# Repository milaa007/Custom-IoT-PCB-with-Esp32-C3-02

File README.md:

Project Summary: Custom 4 LayerIoT PCB with ESP32-C3-02 and TP4056 Li-ion Charger
This project involves the design and development of a custom PCB for an IoT application powered by the ESP32-C3-02 SoC. The board includes integrated power management features using the TP4056 Li-ion battery charger IC, enabling efficient and safe charging of a single-cell Li-ion battery.

Key Features
Microcontroller: ESP32-C3-02 SoC for Wi-Fi and BLE connectivity.
Power Management: TP4056 IC for single-cell Li-ion battery charging with thermal regulation.
Battery Protection: Integrated under-voltage lockout and trickle charging.
Sensors and Modules:
BME280 for temperature, humidity, and pressure sensing.
Ambient light and sound sensors.
Mini SD card reader for data storage.
Flash memory for additional storage.
Display: I2C OLED for real-time data visualization.
Power Inputs:
USB-C connector for charging and data transfer.
LiPo battery connector with onboard charging circuitry.
Indicators: LED indicators for charge status (charging and full).

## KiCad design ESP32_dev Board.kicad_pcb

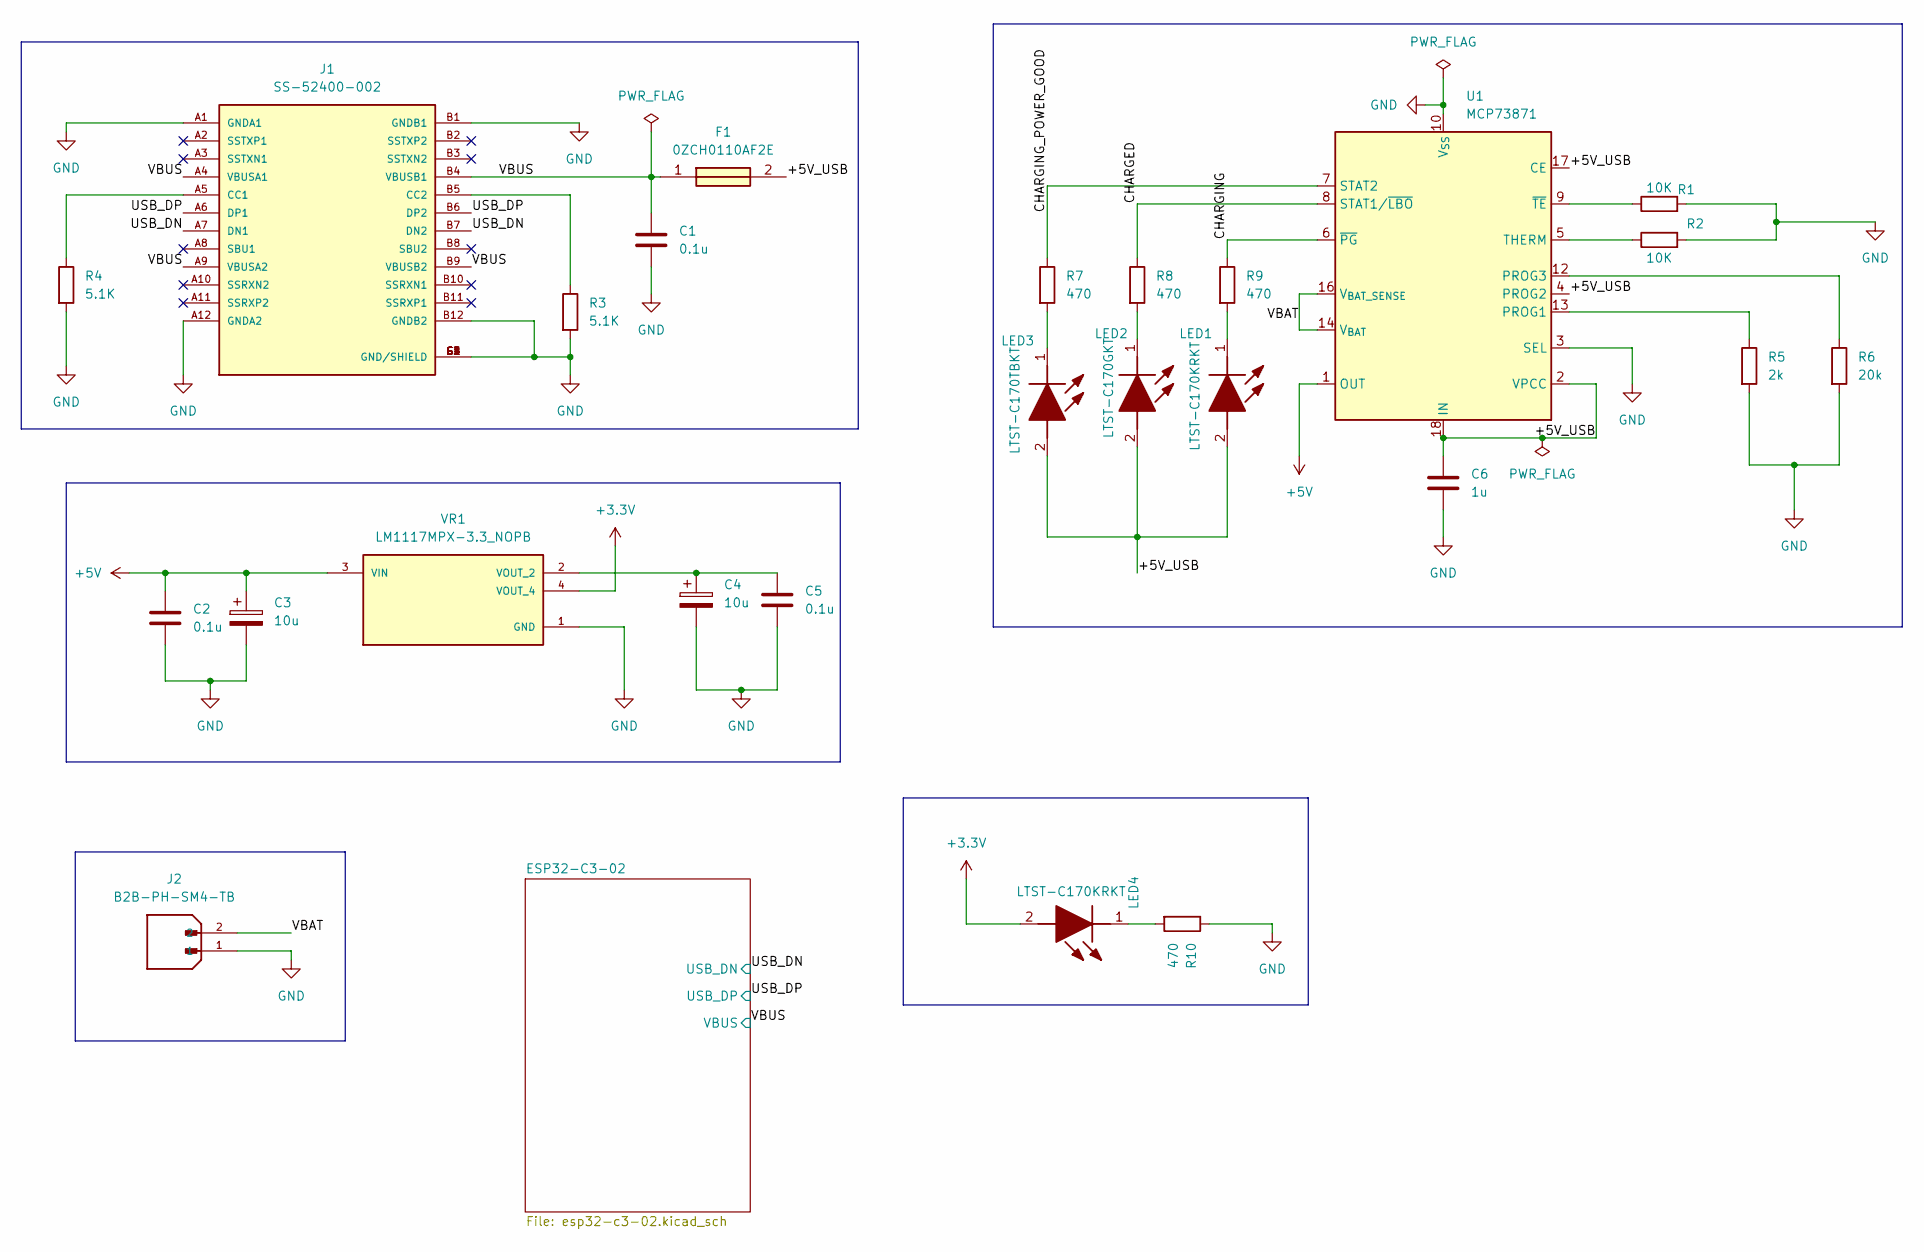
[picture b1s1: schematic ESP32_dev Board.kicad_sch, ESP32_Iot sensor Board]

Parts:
C1, C2, C5: 0.1u; C_0805_2012Metric
C3, C4: 10u; T491A
C6: 1u; C_0805_2012Metric
F1: 0ZCH0110AF2E; FUSC3226X100N; Manufacturer_Part_Number 0ZCH0110AF2E
J1: SS-52400-002; BELFUSE_SS-52400-002; PARTREV A0
J2: B2B-PH-SM4-TB; JST_B2B-PH-SM4-TB; PARTREV N/A
LED1, LED4: LTST-C170KRKT; LEDC2012X120N; Manufacturer_Part_Number LTST-C170KRKT; Mouser Part Number 859-LTST-C170KRKT
LED2: LTST-C170GKT; LEDC2012X120N; Manufacturer_Part_Number LTST-C170GKT; Mouser Part Number 859-LTST-C170GKT
LED3: LTST-C170TBKT; LEDC2012X120N; Manufacturer_Part_Number LTST-C170TBKT; Mouser Part Number 859-LTST-C170TBKT
R1, R2: 10K; R_0805_2012Metric
R3, R4: 5.1K; R_0805_2012Metric
R5: 2k; R_0805_2012Metric
R6: 20k; R_0805_2012Metric
R7, R8, R9, R10: 470; R_0805_2012Metric
U1: MCP73871; QFN-20-1EP_4x4mm_P0.5mm_EP2.5x2.5mm
VR1: LM1117MPX-3.3_NOPB; VREG_LM1117MPX-3.3_NOPB; PARTREV O

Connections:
+5V: C2.1, C3.1, U1.1 (OUT), U1.20 (OUT), VR1.3 (VIN)
/+5V_USB: C6.1, F1.2, LED1.2 (A), LED2.2 (A), LED3.2 (A), U1.2 (VPCC), U1.4 (PROG2), U1.17 (CE), U1.18 (IN), U1.19 (IN)
/CHARGED: R8.1, U1.8 (STAT1/~LBO)
/CHARGING: R9.1, U1.6 (~PG)
/CHARGING_POWER_GOOD: R7.1, U1.7 (STAT2)
/USB_DN: J1.A7 (DN1), J1.B7 (DN2); also elsewhere on the board
/USB_DP: J1.A6 (DP1), J1.B6 (DP2); also elsewhere on the board
/VBAT: J2.2, U1.14 (V_{BAT}), U1.15 (V_{BAT}), U1.16 (V_{BAT_SENSE})
/VBUS: C1.1, F1.1, J1.A4 (VBUSA1), J1.A9 (VBUSA2), J1.B4 (VBUSB1), J1.B9 (VBUSB2); also elsewhere on the board
GND: C1.2, C2.2, C3.2, C4.2, C5.2, C6.2, J1.A1 (GNDA1), J1.A12 (GNDA2), J1.B1 (GNDB1), J1.B12 (GNDB2), J1.G1 (GND/SHIELD), J1.G2 (GND/SHIELD), J1.G3 (GND/SHIELD), J1.G4 (GND/SHIELD), J1.S1 (GND/SHIELD), J1.S2 (GND/SHIELD), J1.S3 (GND/SHIELD), J1.S4 (GND/SHIELD), J2.1, R1.2, R2.2, R3.2, R4.2, R5.2, R6.2, R10.1, U1.3 (SEL), U1.10 (V_{SS}), U1.11 (V_{SS}), U1.21 (V_{SS}), VR1.1 (GND); also elsewhere on the board
unnamed: J1.A5 (CC1), R4.1
unnamed: J1.B5 (CC2), R3.1
unnamed: LED1.1 (K), R9.2
unnamed: LED2.1 (K), R8.2
unnamed: LED3.1 (K), R7.2
unnamed: LED4.1 (K), R10.2
unnamed: R5.1, U1.13 (PROG1)
unnamed: R6.1, U1.12 (PROG3)
unnamed: R2.1, U1.5 (THERM)
unnamed: R1.1, U1.9 (~TE)

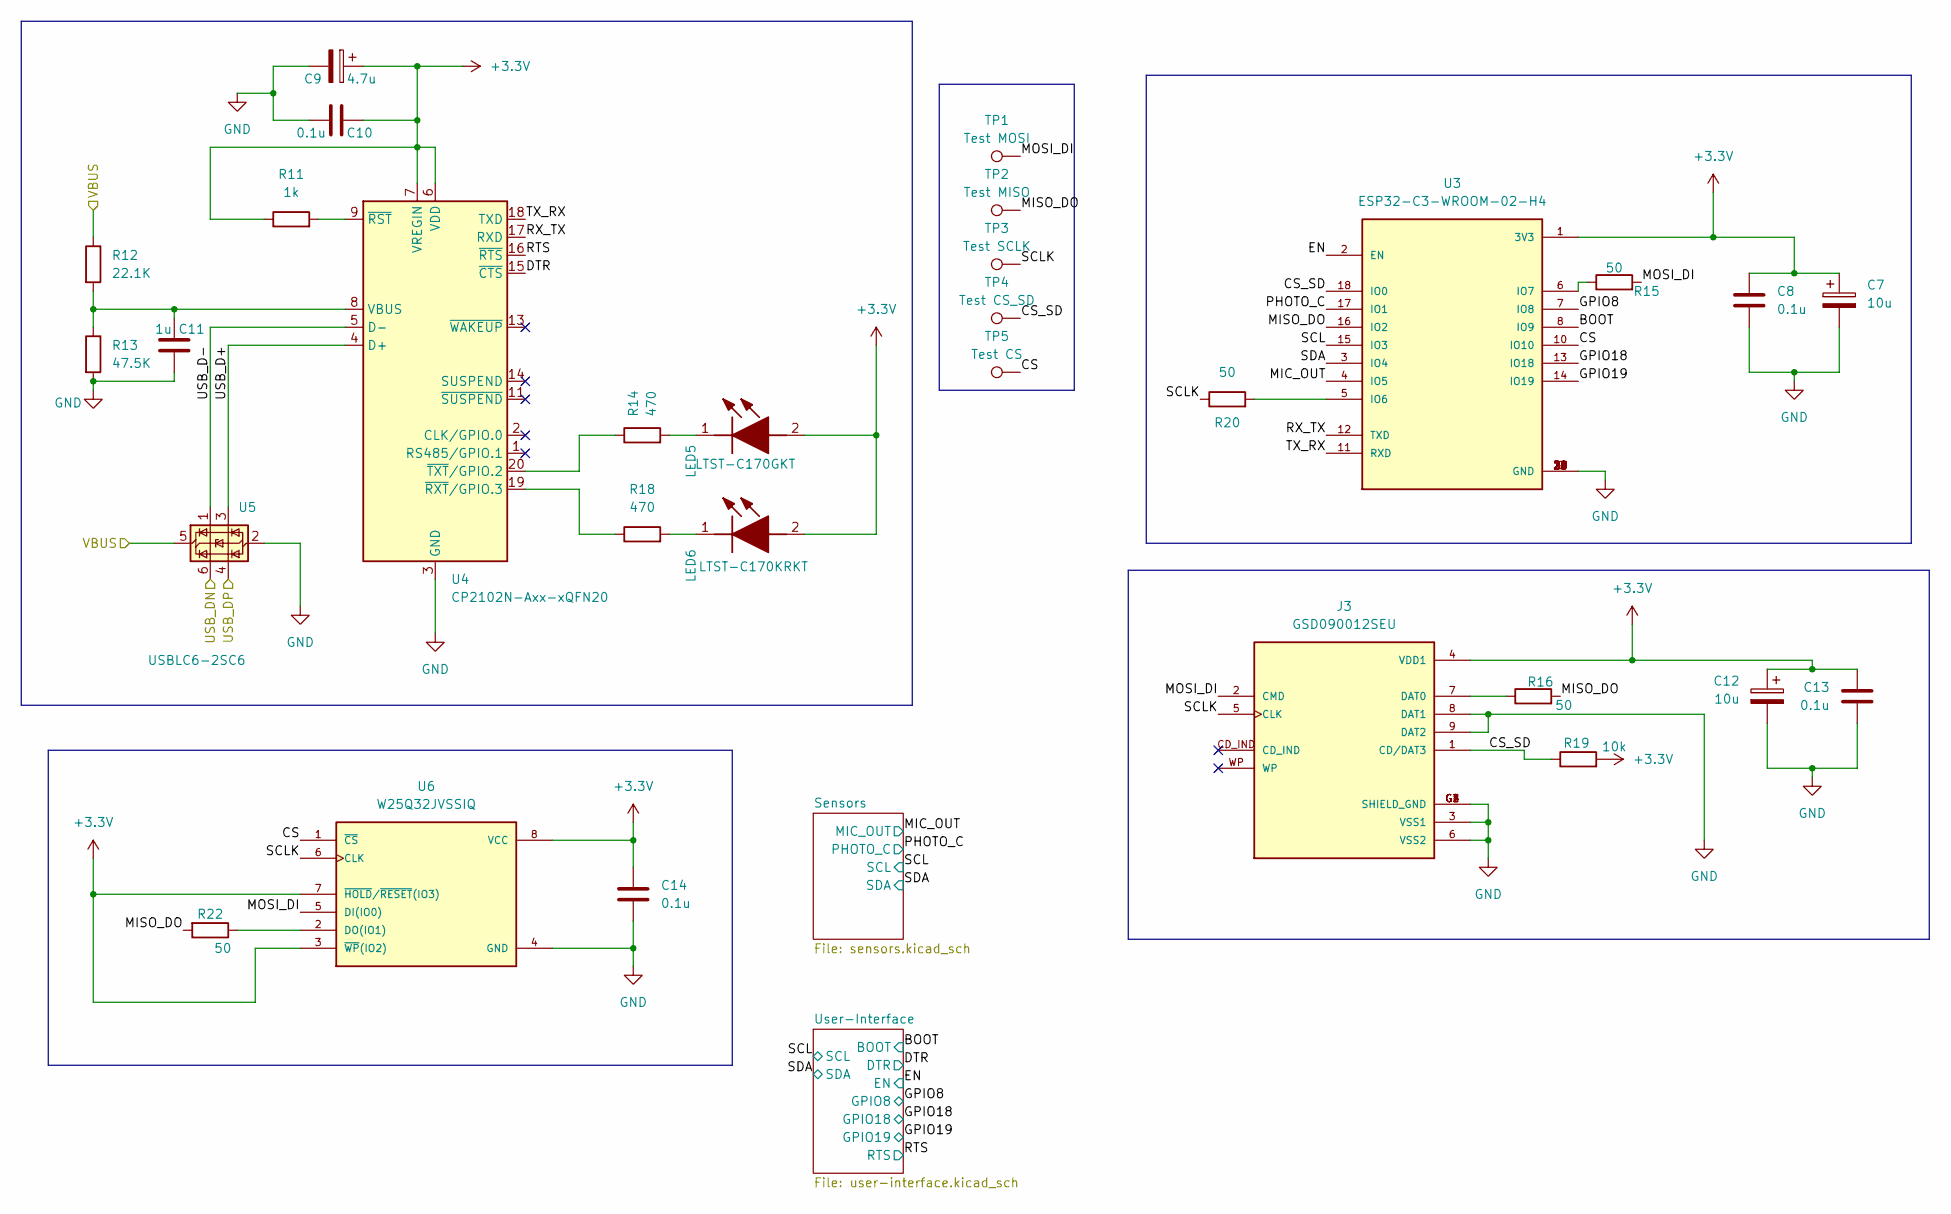
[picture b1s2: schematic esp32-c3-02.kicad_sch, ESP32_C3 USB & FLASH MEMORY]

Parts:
C7, C12: 10u; T491A
C8, C10, C13, C14: 0.1u; C_0805_2012Metric
C9: 4.7u; T491A
C11: 1u; C_0805_2012Metric
J3: GSD090012SEU; AMPHENOL_GSD090012SEU; PARTREV E
LED5: LTST-C170GKT; LEDC2012X120N; Manufacturer_Part_Number LTST-C170GKT; Mouser Part Number 859-LTST-C170GKT
LED6: LTST-C170KRKT; LEDC2012X120N; Manufacturer_Part_Number LTST-C170KRKT; Mouser Part Number 859-LTST-C170KRKT
R11: 1k; R_0805_2012Metric
R12: 22.1K; R_0805_2012Metric
R13: 47.5K; R_0805_2012Metric
R14, R18: 470; R_0805_2012Metric
R15, R16, R20, R22: 50; R_0805_2012Metric
R19: 10k; R_0805_2012Metric
TP1: Test MOSI; TestPoint_Pad_D1.0mm
TP2: Test MISO; TestPoint_Pad_D1.0mm
TP3: Test SCLK; TestPoint_Pad_D1.0mm
TP4: Test CS_SD; TestPoint_Pad_D1.0mm
TP5: Test CS; TestPoint_Pad_D1.0mm
U3: ESP32-C3-WROOM-02-H4; MODULE_ESP32-C3-WROOM-02-H4
U4: CP2102N-Axx-xQFN20; QFN-20-1EP_3x4mm_P0.5mm_EP1.65x2.65mm
U5: USBLC6-2SC6; SOT-23-6
U6: W25Q32JVSSIQ; SOIC127P790X216-8N; M_PART_NUMBER W25QXX

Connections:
/ESP32-C3-02/BOOT: U3.8 (IO9); also elsewhere on the board
/ESP32-C3-02/CS: TP5.1 (1_1), U3.10 (IO10), U6.1 (~CS)
/ESP32-C3-02/CS_SD: J3.1 (CD/DAT3), R19.1, TP4.1 (1_1), U3.18 (IO0)
/ESP32-C3-02/DTR: U4.15 (~CTS); also elsewhere on the board
/ESP32-C3-02/EN: U3.2 (EN); also elsewhere on the board
/ESP32-C3-02/GPIO8: U3.7 (IO8); also elsewhere on the board
/ESP32-C3-02/GPIO18: U3.13 (IO18); also elsewhere on the board
/ESP32-C3-02/GPIO19: U3.14 (IO19); also elsewhere on the board
/ESP32-C3-02/MIC_OUT: U3.4 (IO5); also elsewhere on the board
/ESP32-C3-02/MISO_DO: R16.2, R22.2, TP2.1 (1_1), U3.16 (IO2)
/ESP32-C3-02/MOSI_DI: J3.2 (CMD), R15.2, TP1.1 (1_1), U6.5 (DI(IO0))
/ESP32-C3-02/PHOTO_C: U3.17 (IO1); also elsewhere on the board
/ESP32-C3-02/RTS: U4.16 (~RTS); also elsewhere on the board
/ESP32-C3-02/RX_TX: U3.12 (TXD), U4.17 (RXD)
/ESP32-C3-02/SCL: U3.15 (IO3); also elsewhere on the board
/ESP32-C3-02/SCLK: J3.5 (CLK), R20.1, TP3.1 (1_1), U6.6 (CLK)
/ESP32-C3-02/SDA: U3.3 (IO4); also elsewhere on the board
/ESP32-C3-02/TX_RX: U3.11 (RXD), U4.18 (TXD)
/ESP32-C3-02/USB_D+: U4.4 (D+), U5.3 (I/O2)
/ESP32-C3-02/USB_D-: U4.5 (D-), U5.1 (I/O1)
/USB_DN: U5.6 (I/O1); also elsewhere on the board
/USB_DP: U5.4 (I/O2); also elsewhere on the board
/VBUS: R12.1, U5.5 (VBUS); also elsewhere on the board
GND: C7.2, C8.2, C9.2, C10.1, C11.2, C12.2, C13.2, C14.2, J3.3 (VSS1), J3.6 (VSS2), J3.8 (DAT1), J3.9 (DAT2), J3.G1 (SHIELD_GND), J3.G2 (SHIELD_GND), J3.G3 (SHIELD_GND), J3.G4 (SHIELD_GND), R13.2, U3.9 (GND), U3.19 (GND), U3.20 (GND), U3.21 (GND), U3.22 (GND), U3.23 (GND), U3.24 (GND), U3.25 (GND), U3.26 (GND), U3.27 (GND), U3.28 (GND), U3.29 (GND), U3.30 (GND), U3.31 (GND), U3.32 (GND), U3.33 (GND), U3.34 (GND), U3.35 (GND), U3.36 (GND), U3.37 (GND), U3.38 (GND), U3.39 (GND), U4.3 (GND), U4.12 (GND), U4.21 (GND), U5.2 (GND), U6.4 (GND); also elsewhere on the board
unnamed: J3.7 (DAT0), R16.1
unnamed: LED5.1 (K), R14.2
unnamed: LED6.1 (K), R18.2
unnamed: R20.2, U3.5 (IO6)
unnamed: R15.1, U3.6 (IO7)
unnamed: C11.1, R12.2, R13.1, U4.8 (VBUS)
unnamed: R11.2, U4.9 (~RST)
unnamed: R18.1, U4.19 (~RXT/GPIO.3)
unnamed: R14.1, U4.20 (~TXT/GPIO.2)
unnamed: R22.1, U6.2 (DO(IO1))

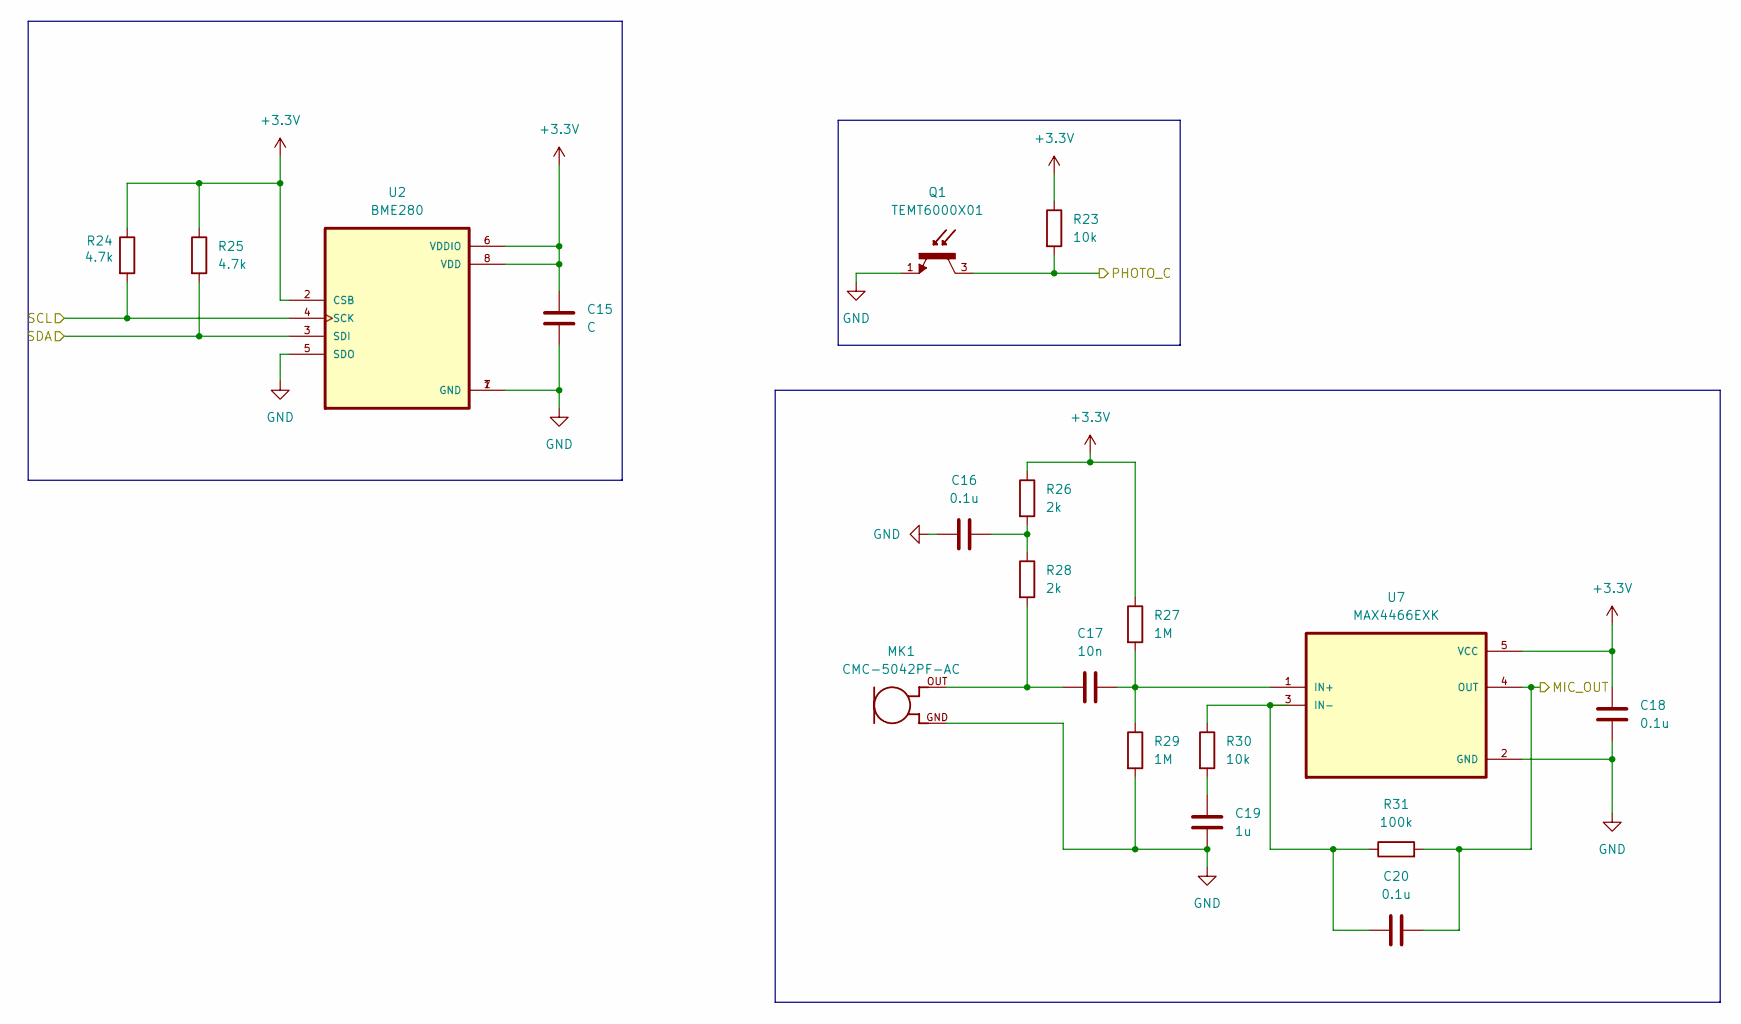
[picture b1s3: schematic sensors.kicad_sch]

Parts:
C15: C; C_0805_2012Metric
C16, C18, C20: 0.1u; C_0805_2012Metric
C17: 10n; C_0805_2012Metric
C19: 1u; C_0805_2012Metric
MK1: CMC-5042PF-AC; CUI_CMC-5042PF-AC
Q1: TEMT6000X01; TRANS_TEMT6000X01; PARTREV 1.9
R23, R30: 10k; R_0805_2012Metric
R24, R25: 4.7k; R_0805_2012Metric
R26, R28: 2k; R_0805_2012Metric
R27, R29: 1M; R_0805_2012Metric
R31: 100k; R_0805_2012Metric
U2: BME280; PSON65P250X250X100-8N
U7: MAX4466EXK; SOT65P210X110-5N

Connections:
/ESP32-C3-02/MIC_OUT: C20.1, R31.2, U7.4 (OUT); also elsewhere on the board
/ESP32-C3-02/PHOTO_C: Q1.3, R23.2; also elsewhere on the board
/ESP32-C3-02/SCL: R24.2, U2.4 (SCK); also elsewhere on the board
/ESP32-C3-02/SDA: R25.2, U2.3 (SDI); also elsewhere on the board
GND: C15.2, C16.2, C18.2, C19.2, MK1.GND, Q1.1, R29.2, U2.1 (GND), U2.5 (SDO), U2.7 (GND), U7.2 (GND); also elsewhere on the board
unnamed: C16.1, R26.2, R28.1
unnamed: C17.1, MK1.OUT, R28.2
unnamed: C19.1, R30.2
unnamed: C17.2, R27.2, R29.1, U7.1 (IN+)
unnamed: C20.2, R30.1, R31.1, U7.3 (IN-)

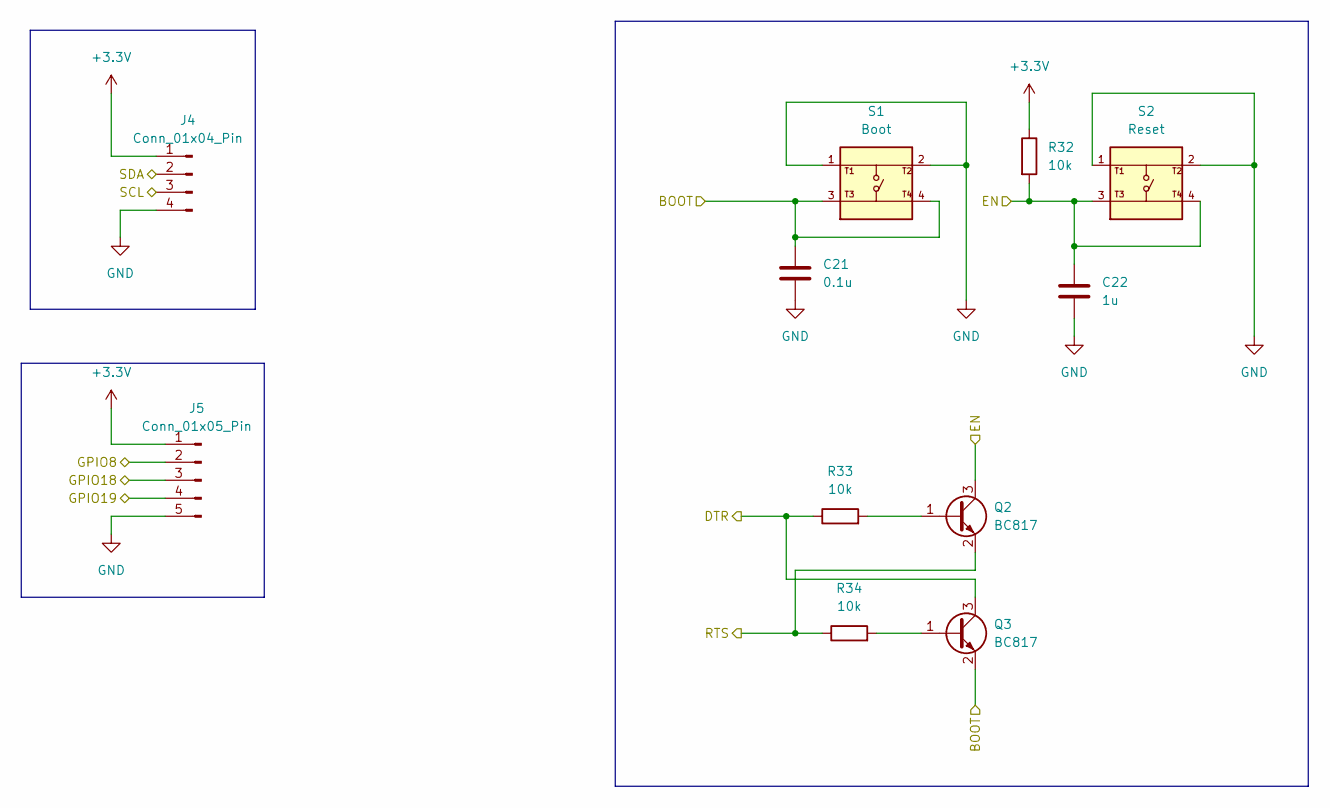
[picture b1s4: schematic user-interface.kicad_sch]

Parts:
C21: 0.1u; C_0805_2012Metric
C22: 1u; C_0805_2012Metric
J4: Conn_01x04_Pin; PinHeader_1x04_P2.54mm_Vertical
J5: Conn_01x05_Pin; PinHeader_1x05_P2.54mm_Vertical
Q2, Q3: BC817; SOT-23
R32, R33, R34: 10k; R_0805_2012Metric
S1: Boot; SW_USLPT2819DT2TR; PARTREV P
S2: Reset; SW_USLPT2819DT2TR; PARTREV P

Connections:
/ESP32-C3-02/BOOT: C21.1, Q3.2 (E), S1.3, S1.4; also elsewhere on the board
/ESP32-C3-02/DTR: Q3.3 (C), R33.1; also elsewhere on the board
/ESP32-C3-02/EN: C22.1, Q2.3 (C), R32.2, S2.3, S2.4; also elsewhere on the board
/ESP32-C3-02/GPIO8: J5.2; also elsewhere on the board
/ESP32-C3-02/GPIO18: J5.3; also elsewhere on the board
/ESP32-C3-02/GPIO19: J5.4; also elsewhere on the board
/ESP32-C3-02/RTS: Q2.2 (E), R34.1; also elsewhere on the board
/ESP32-C3-02/SCL: J4.3; also elsewhere on the board
/ESP32-C3-02/SDA: J4.2; also elsewhere on the board
GND: C21.2, C22.2, J4.4, J5.5, S1.1, S1.2, S2.1, S2.2; also elsewhere on the board
unnamed: Q2.1 (B), R33.2
unnamed: Q3.1 (B), R34.2

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
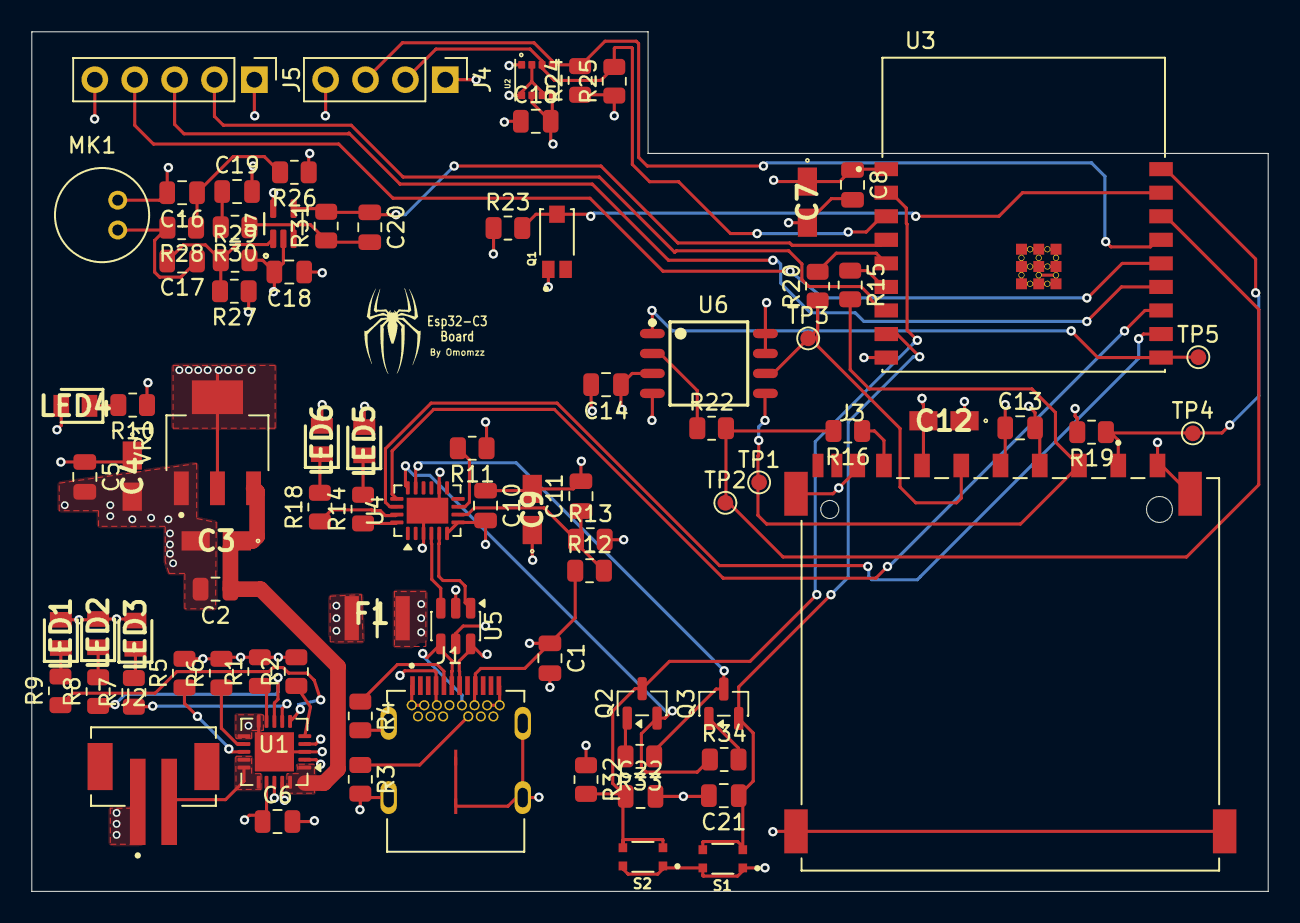
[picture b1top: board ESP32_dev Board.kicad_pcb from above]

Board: 4 copper layers, 78.8 x 54.8 mm, 85 parts (0 on the bottom side), 58 nets.
